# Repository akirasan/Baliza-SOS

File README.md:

# Baliza S.O.S vial
Baliza SOS vial, para señalizar en caso de emergencia.

Toda la info del proyecto en el post [http://akirasan.net/baliza-vial-sos/](http://akirasan.net/baliza-vial-sos/)

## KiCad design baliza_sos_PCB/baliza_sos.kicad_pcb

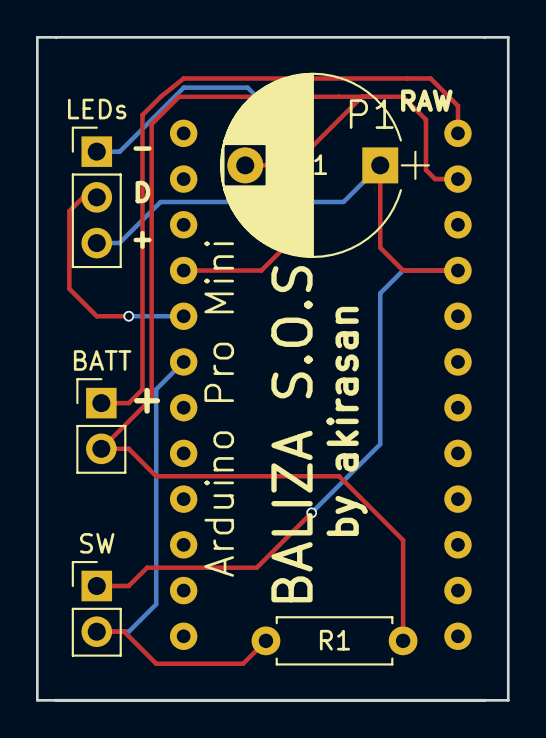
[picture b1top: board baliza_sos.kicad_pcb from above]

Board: 2 copper layers, 26.2 x 36.8 mm, 6 parts (0 on the bottom side), 6 nets.

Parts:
BATT: BATT; Pin_Header_Straight_1x02_Pitch2.54mm
C1: CP; CP_Radial_D10.0mm_P7.50mm
LEDs: LEDs; Pin_Header_Straight_1x03_Pitch2.54mm
P1: Arduino Pro Mini; ArduProMini-6
R1: R; R_Axial_DIN0207_L6.3mm_D2.5mm_P7.62mm_Horizontal
SW: SW1; Pin_Header_Straight_1x02_Pitch2.54mm

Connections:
GND: BATT.2, C1.2, P1.20, R1.2
unnamed: C1.1, LEDs.3, P1.22, SW.1
unnamed: LEDs.1, P1.10
unnamed: LEDs.2, P1.11
unnamed: P1.12, R1.1, SW.2
VCC: BATT.1, P1.19

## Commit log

2017-12-29 version inicial de todo el proyecto
2017-12-30 version mejorada
2017-12-31 tapa superior con mini pushbutton
2018-01-03 adaptacion codigo a pushbutton
2018-01-05 PCB info
